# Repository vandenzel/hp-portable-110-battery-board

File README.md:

# HP Portable 110 Battery Board

A replacement board to stick onto the battery pack of a HP Portable 110 computer. But with some SMD parts. Also the 3 pin header should be a locking/latching part instead of "just" a pin header.

I didn't have a 3D image for the F1 fuse, or the J3 stud.

## Parts list

On PCB

| Part | Description             | Notes                                                                           |
| ---- | ----------------------- | ------------------------------------------------------------------------------- |
| D1   | 1N4001                  | this should be a D_SMA package                                                  |
| F1   | 0.5A                    | [Mouser](https://mou.sr/42zEMhM)                                                                            |
| J1   | header 1x2 2.54mm pitch | pinheader, or JST-XH, or wires soldered directly to PCB                         |
| J2   | header 1x3 2.54mm pitch | plain pinheader or something compatible with the locking connector              |
| J3   | screw terminal          | Press-fit M3 stud 6mm long ([PEM KFH-M3-6ET at Mouser](https://mou.sr/3RKMalD)) |
| SW1  | Reset switch            | Tact switch                                                                     |

External to PCB

| Part | Description                | Notes                                                 |
| ---- | -------------------------- | ----------------------------------------------------- |
| BT'1 | 6V 2.5Ah Lead Acid battery | i.e. LP 6-2.8 VRLA AGM Battery                        |
| J'1  | 1x02 2.54 pitch (female)   | could be omitted and wires soldered directly to board |

The battery usually has spade connectors, and the amperage is not really high, so basically any wire with a spade (a.k.a AMP) connector can be used. To connect it to the circuit board you can use a pinheader (like in the image), or a (2.54mm pitch) JST-XH connector, or just solder the wire to the respective holes.

If all goes well, the circuit board can be stuck to the battery using a piece of double sided, foam core sticky tape. Foam core to allow for the through-hole pins. Before sticking it on, check the fit in the battery compartment of the Portable 110.

## Dependencies:

- KiCad (obviously), version 8.0 or later.
- The [Fabrication Toolkit](https://github.com/bennymeg/Fabrication-Toolkit) plugin for KiCad.

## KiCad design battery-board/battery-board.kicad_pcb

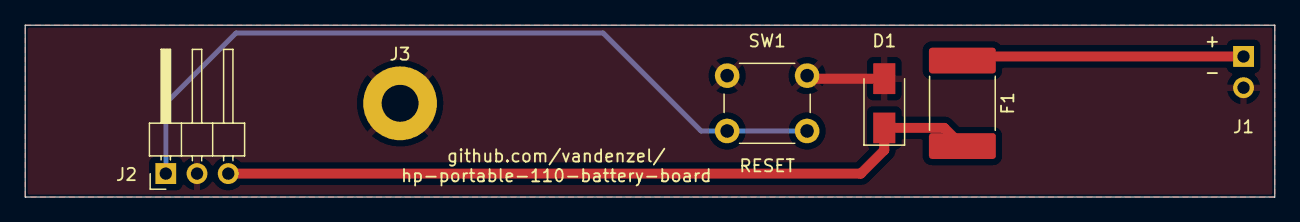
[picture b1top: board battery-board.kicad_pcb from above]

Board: 2 copper layers, 101.6 x 14.0 mm, 6 parts (1 on the bottom side), 4 nets.

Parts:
D1: 1N4001; D_SMA
F1: 0.5A; Fuse_2920_7451Metric_Pad2.10x5.45mm_HandSolder
J1: Conn_01x02_Male; PinHeader_1x02_P2.54mm_Vertical
J2: Conn_01x03; PinHeader_1x03_P2.54mm_Horizontal
J3: Screw_Terminal_01x01; M3x6 Mounting stud pressfit
SW1: RESET; SW_PUSH_6mm

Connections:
/GND: D1.2 (A), J1.2, J2.2, J3.1, SW1.1
/VBB: F1.1, J1.1
/VCC: D1.1 (K), F1.2, J2.3
/~RESET: J2.1, SW1.2

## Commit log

2025-04-18 gitignore...
2025-04-18 frist
2025-04-18 updated to a different fuse
